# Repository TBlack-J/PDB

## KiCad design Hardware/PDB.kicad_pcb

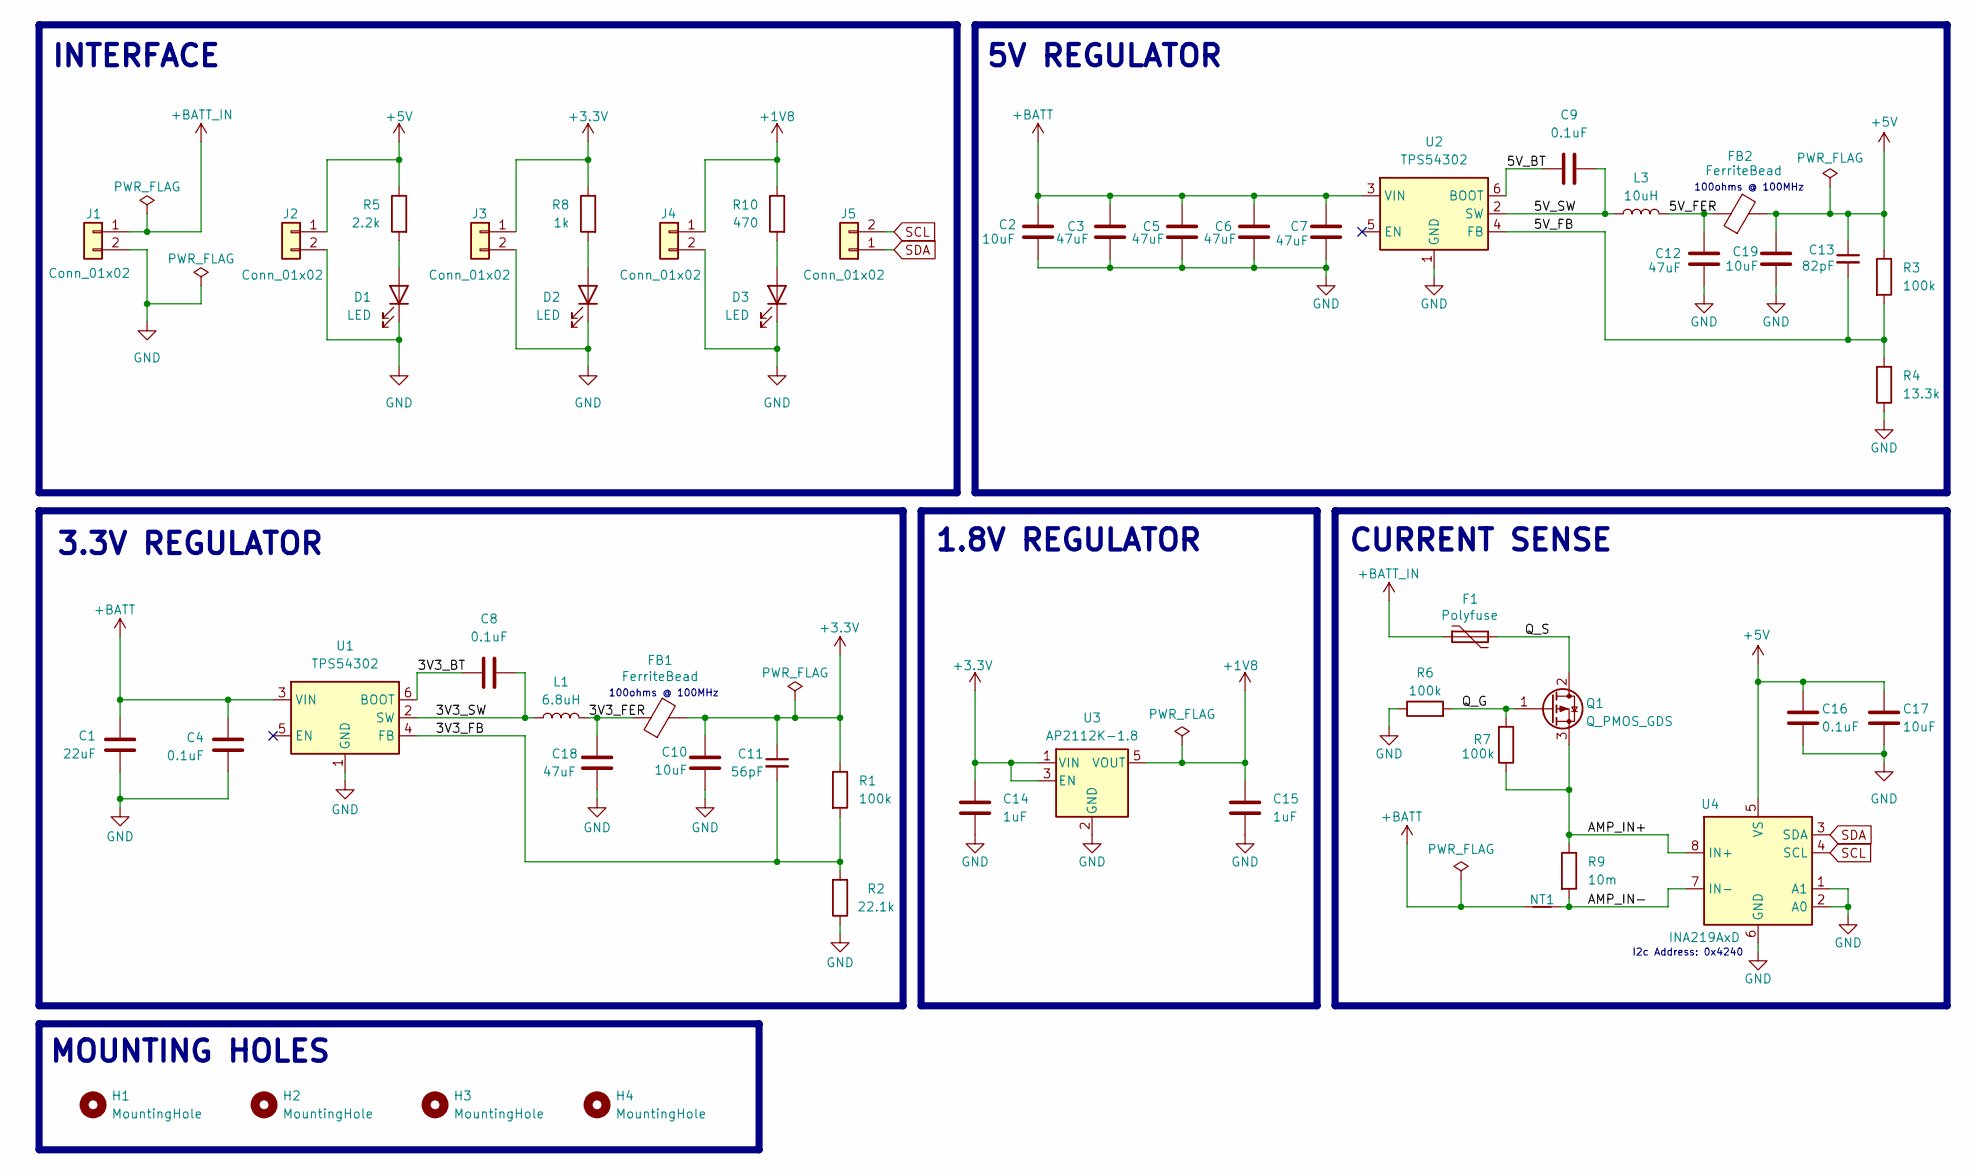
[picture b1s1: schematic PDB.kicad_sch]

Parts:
C1: 22uF; C_1206_3216Metric
C2, C10, C17, C19: 10uF; C_1206_3216Metric
C3, C5, C6, C7, C12, C18: 47uF; C_1206_3216Metric
C4, C8, C9, C16: 0.1uF; C_0805_2012Metric
C11: 56pF; C_0603_1608Metric
C13: 82pF; C_0603_1608Metric
C14, C15: 1uF; C_0805_2012Metric
D1, D2, D3: LED; LED_0805_2012Metric
F1: Polyfuse; Fuse_1812_4532Metric
FB1, FB2: FerriteBead; L_0805_2012Metric; MPN MPZ2012S101AT000
H1, H2, H3, H4: MountingHole; MountingHole_2.1mm
J1, J2, J3, J4, J5: Conn_01x02; PinHeader_1x02_P2.54mm_Vertical
L1: 6.8uH; L_6.3x6.3_H3
L3: 10uH; L_6.3x6.3_H3
NT1: NetTie_2; NetTie-2_SMD_Pad0.6mm
Q1: Q_PMOS_GDS; SOIC-8_3.9x4.9mm_P1.27mm
R1, R3, R6, R7: 100k; R_0805_2012Metric
R2: 22.1k; R_0805_2012Metric
R4: 13.3k; R_0805_2012Metric
R5: 2.2k; R_0805_2012Metric
R8: 1k; R_0805_2012Metric
R9: 10m; R_2512_6332Metric
R10: 470; R_0805_2012Metric
U1, U2: TPS54302; SOT-23-6
U3: AP2112K-1.8; SOT-23-5
U4: INA219AxD; SOIC-8_3.9x4.9mm_P1.27mm

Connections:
+1V8: C15.2, J4.1, R10.1, U3.5 (VOUT)
+3.3V: C10.1, C11.1, C14.1, FB1.2, J3.1, R1.1, R8.1, U3.1 (VIN), U3.3 (EN)
+5V: C13.1, C16.2, C17.2, C19.1, FB2.2, J2.1, R3.1, R5.1, U4.5 (VS)
+BATT: C1.1, C2.1, C3.1, C4.2, C5.1, C6.1, C7.1, NT1.1, U1.3 (VIN), U2.3 (VIN)
+BATT_IN: F1.1, J1.1
/3V3_BT: C8.1, U1.6 (BOOT)
/3V3_FB: C11.2, R1.2, R2.2, U1.4 (FB)
/3V3_SW: C8.2, L1.1, U1.2 (SW)
/5V_BT: C9.1, U2.6 (BOOT)
/5V_FB: C13.2, R3.2, R4.2, U2.4 (FB)
/5V_SW: C9.2, L3.1, U2.2 (SW)
/AMP_IN+: Q1.3 (S), R7.1, R9.1, U4.8 (IN+)
/AMP_IN-: NT1.2, R9.2, U4.7 (IN-)
/Q_G: Q1.1 (G), R6.2, R7.2
/Q_S: F1.2, Q1.2 (D)
GND: C1.2, C2.2, C3.2, C4.1, C5.2, C6.2, C7.2, C10.2, C12.2, C14.2, C15.1, C16.1, C17.1, C18.2, C19.2, D1.1 (K), D2.1 (K), D3.1 (K), J1.2, J2.2, J3.2, J4.2, R2.1, R4.1, R6.1, U1.1 (GND), U2.1 (GND), U3.2 (GND), U4.1 (A1), U4.2 (A0), U4.6 (GND)
unnamed: C12.1, FB2.1, L3.2
unnamed: C18.1, FB1.1, L1.2
unnamed: D1.2 (A), R5.2
unnamed: D2.2 (A), R8.2
unnamed: D3.2 (A), R10.2
SCL: J5.2, U4.4 (SCL)
SDA: J5.1, U4.3 (SDA)

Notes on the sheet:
MOUNTING HOLES
INTERFACE
CURRENT SENSE
100ohms @ 100MHz
5V REGULATOR
1.8V REGULATOR
3.3V REGULATOR
I2c Address: 0x4240

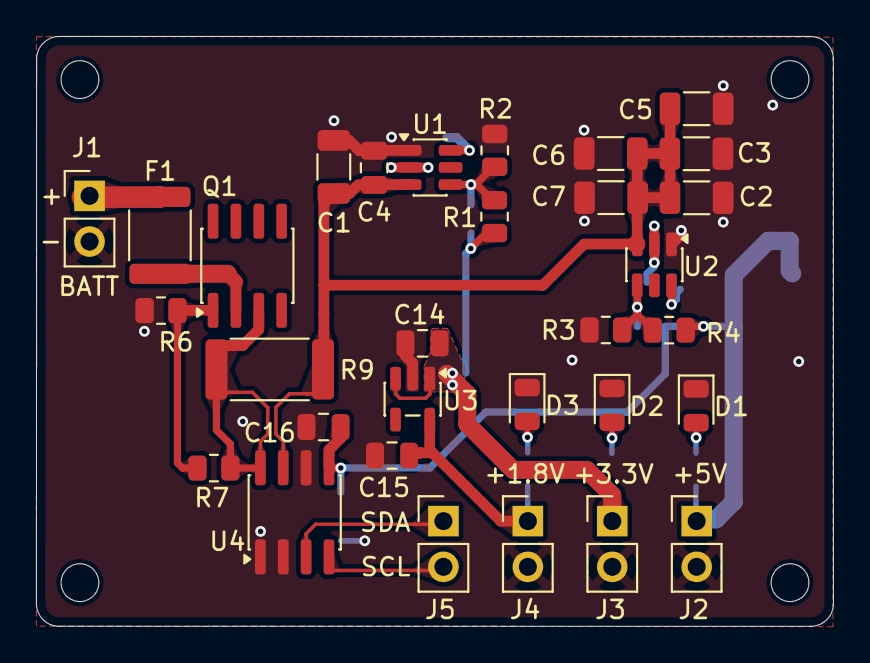
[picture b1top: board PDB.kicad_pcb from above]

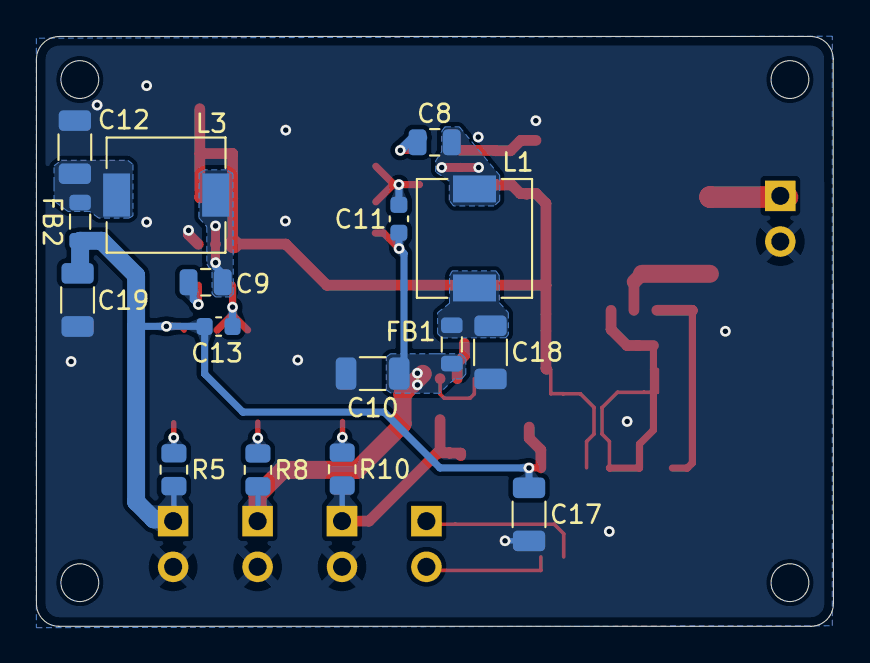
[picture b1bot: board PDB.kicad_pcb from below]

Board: 2 copper layers, 44.3 x 32.8 mm, 52 parts (16 on the bottom side), 23 nets.

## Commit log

2026-04-11 Updated schematic and PCB
2026-04-11 Added silkscreen labels
2026-04-11 Small fixes
2026-04-11 More small changes
2026-04-11 Even more small changes
2026-04-11 More changes
